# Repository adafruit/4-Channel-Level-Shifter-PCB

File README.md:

# Adafruit 4 Channel Level Shifter PCB
<a href="http://www.adafruit.com/products/757"><br/>
Click here to purchase one from the Adafruit shop</a>

This level shifter board combines the ease-of-use of the bi-directional TXB0108 with an I2C-compatible FET design following NXP's app note.

This breakout has 4 BSS138 FETs with 10K pullups. It works down to 1.8V on the low side, and up to 10V on the high side. The 10K's do make the interface a little more sluggish than using a TXB0108 or 74LVC245 so we suggest checking those out if you need high-speed transfer.

While we designed it for use with I2C, this works as well for  TTL Serial,  slow <2MHz SPI, and any other digital interface both uni-directional and bidirectional. Comes with a fully assembled, and tested PCB with 4 full bidirectional converter lines as well as 2 pieces of 6-pin header you can solder on to plug into a breadboard or perfboard.

These are the Eagle CAD files for the Adafruit BSS138-based 4 channel level shifter

### License

Adafruit invests time and resources providing this open source design, please support Adafruit and open-source hardware by purchasing products from [Adafruit](https://www.adafruit.com)!

All text above must be included in any redistribution

Designed by Limor Fried/Ladyada for Adafruit Industries.
Creative Commons Attribution/Share-Alike, all text above must be included in any redistribution. 
See license.txt for additional information.

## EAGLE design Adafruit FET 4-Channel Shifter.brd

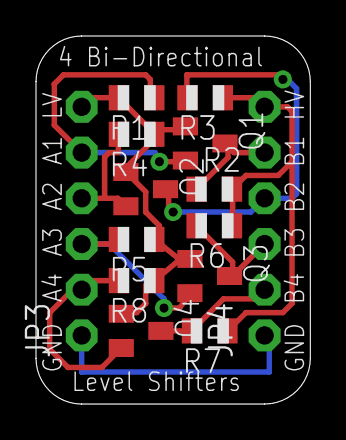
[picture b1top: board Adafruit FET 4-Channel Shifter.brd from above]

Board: 2 copper layers, 15.2 x 20.4 mm, 15 parts (1 on the bottom side), 11 nets.

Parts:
JP3, JP4: 1X06-CLEANBIG
Q1, Q2, Q3, Q4: BSS138; SOT23
R1, R2, R3, R4, R5, R6, R7, R8: 10K; R0805
U$1: ADAFRUIT_3.5MM

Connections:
+3V3: JP3.6, Q1.1, Q2.1, Q3.1, Q4.1, R1.2, R4.1, R5.1, R8.1
+5V: JP4.6, R2.2, R3.1, R6.1, R7.1
GND: JP3.1, JP4.1
unnamed: JP4.3, Q3.3, R6.2
unnamed: JP4.5, Q1.3, R2.1
unnamed: JP3.3, Q3.2, R5.2
unnamed: JP3.2, Q4.2, R8.2
unnamed: JP4.2, Q4.3, R7.2
unnamed: JP3.4, Q2.2, R4.2
unnamed: JP4.4, Q2.3, R3.2
unnamed: JP3.5, Q1.2, R1.1

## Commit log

2014-12-10 init
2026-06-03 update file format to XML
